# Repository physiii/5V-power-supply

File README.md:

# 5v power supply with a relay for high voltage control.

Combine this with our other devices to get power and control high-voltage switches.

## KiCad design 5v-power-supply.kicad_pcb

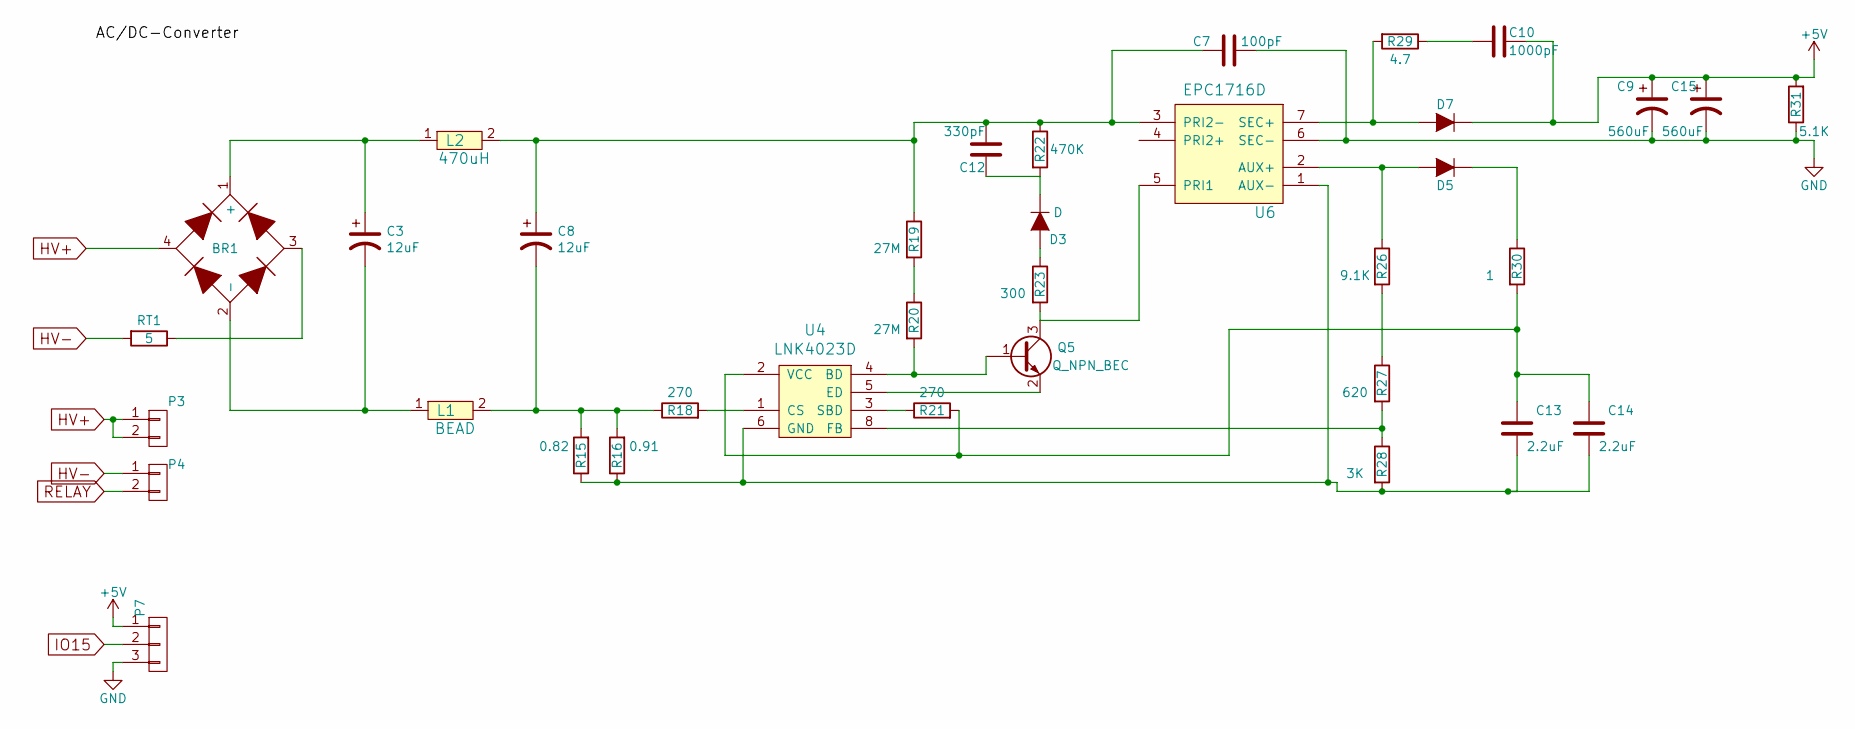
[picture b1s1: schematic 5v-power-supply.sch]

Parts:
BR1: DF08S; DF005S; Part Number DF08SCT
C3, C8: 12uF; C_Radial_D10_L13_P5; Part Number 400AX12MEFC10X12.5
C7: 100pF; C_0603_HandSoldering; Part Number 712-1310-1-ND
C9, C15: 560uF; C_Radial_D8_L11.5_P3.5; Part Number UPW0J561MPD
C10: 1000pF; C_0603_HandSoldering; Part Number GRM188R72E102KW07D
C12: 330pF; C_0805_HandSoldering; Part Number C0805C331KCRACTU
C13, C14: 2.2uF; C_0603_HandSoldering; Part Number C1608X5R1E225K080AB
D3: D; DO-214BA; Part Number GS1MTR
D5: D; SOD-323; Part Number 1N4148WXTPMSCT-ND
D7: D; PMEG45A10EPDAZ-Schottky; Part Number PMEG45A10EPDAZ
L1: BEAD; R_0805_HandSoldering; Part Number MMZ2012D121BT000
L2: 470uH; C_Radial_D10_L13_P5; Part Number BK1608HS330-T
P3, P4: CONN_01X02; pheonix-connector-01x02-5mm; Part Number 277-1667-ND
P7: CONN_01X03; pheonix-connector-01x03-5mm; Part Number ED2792-ND
Q5: Q_NPN_BEC; APT13005SU-G1; Part Number APT13005SU-G1
R15: 0.82; R_0805_HandSoldering; Part Number RL1220S-R82-F
R16: 0.91; R_0805_HandSoldering; Part Number RL1220S-R91-F
R18: 270; R_0805_HandSoldering; Part Number RMCF0805JT270R
R19, R20: 27M; R_1206_HandSoldering; Part Number RV1206JR-0727ML
R21: 270; R_0805_HandSoldering; Part Number RMCF0805JT270RCT-ND
R22: 470K; R_0603_HandSoldering; Part Number RC0603JR-07470KL
R23: 300; R_0603_HandSoldering; Part Number ESR03EZPJ301
R26: 9.1K; R_0603_HandSoldering; Part Number RC0603JR-079K1L
R27: 620; R_0603_HandSoldering; Part Number RC0603JR-07620RL
R28: 3K; R_0603_HandSoldering; Part Number RC0603JR-073KL
R29: 4.7; R_0603_HandSoldering; Part Number RC0603JR-074R7L
R30: 1; R_0603_HandSoldering; Part Number RNCP0603FTD1R00
R31: 5.1K; R_0603_HandSoldering; Part Number RC0603JR-075K1L
RT1: 5; Resistor_Vertical_RM5mm; Part Number SL05 5R001-A
U4: LNK4023D; SO-8; Part Number LNK4023D-TL
U6: EPC1716D; PNK-40230

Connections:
+5V: C9.1, C10.1, C15.1, D7.1 (K), P7.1, R31.2; also elsewhere on the board
GND: C7.2, C9.2, C15.2, P7.3, R31.1, U6.6 (SEC-); also elsewhere on the board
HV+: BR1.4, P3.1, P3.2
HV-: P4.1, RT1.2; also elsewhere on the board
IO15: P7.2; also elsewhere on the board
unnamed: BR1.1 (+), C3.1, L2.1
unnamed: BR1.2 (-), C3.2, L1.1
unnamed: BR1.3, RT1.1
unnamed: C8.2, L1.2, R15.2, R16.2, R18.1
unnamed: C10.2, R29.1
unnamed: C12.1, D3.1 (K), R22.2
unnamed: C7.1, C8.1, C12.2, L2.2, R19.1, R22.1, U6.3 (PRI2-)
unnamed: C13.1, C14.1, R21.2, R30.2, U4.2 (VCC)
unnamed: C13.2, C14.2, R15.1, R16.1, R28.2, U4.6 (GND), U6.1 (AUX-)
unnamed: D3.2 (A), R23.1
unnamed: D5.1 (K), R30.1
unnamed: D5.2 (A), R26.1, U6.2 (AUX+)
unnamed: D7.2 (A), R29.2, U6.7 (SEC+)
unnamed: Q5.1 (B), R20.2, U4.4 (BD)
unnamed: Q5.2 (E), U4.5 (ED)
unnamed: Q5.3 (C), R23.2, U6.5 (PRI1)
unnamed: R18.2, U4.1 (CS)
unnamed: R19.2, R20.1
unnamed: R21.1, U4.3 (SBD)
unnamed: R26.2, R27.1
unnamed: R27.2, R28.1, U4.8 (FB)
RELAY: P4.2; also elsewhere on the board

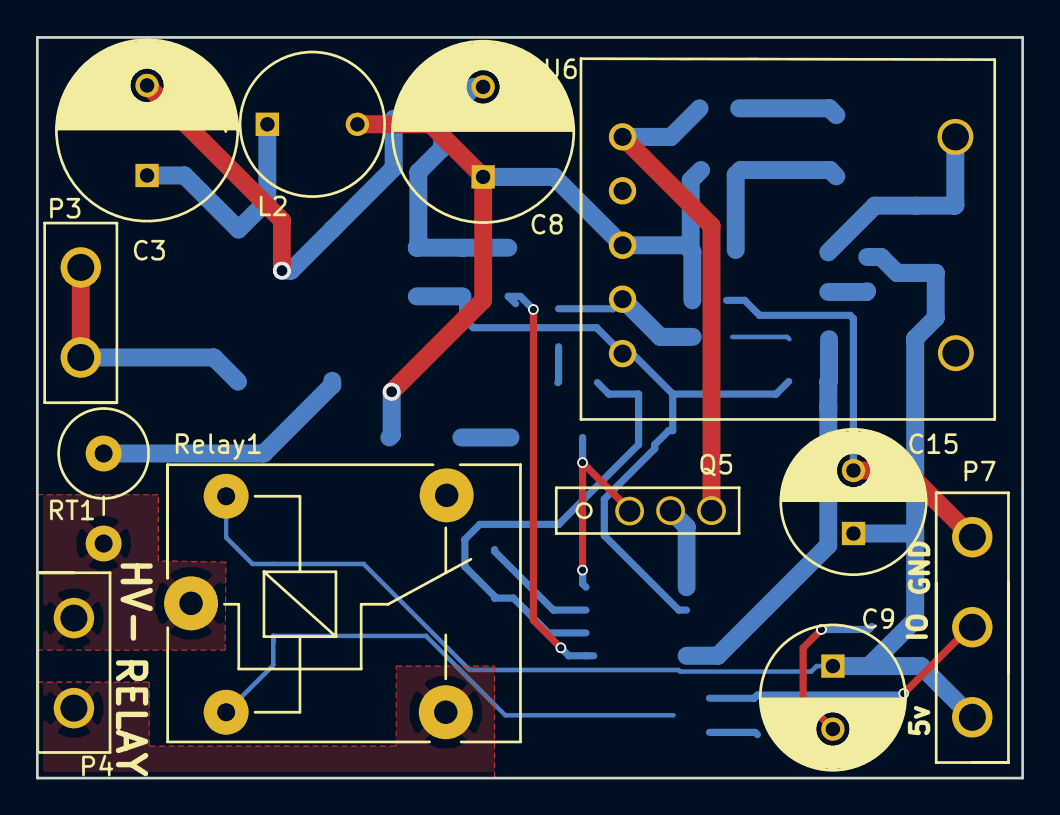
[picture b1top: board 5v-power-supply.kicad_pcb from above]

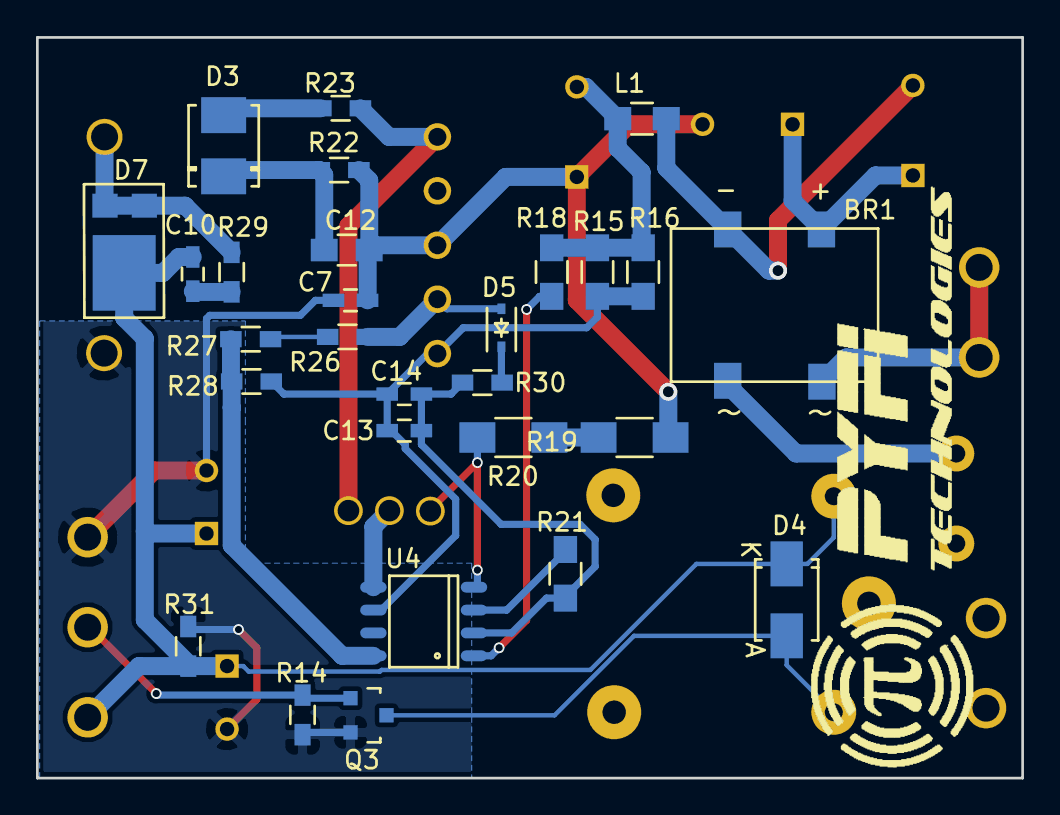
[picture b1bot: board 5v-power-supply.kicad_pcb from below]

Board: 2 copper layers, 54.7 x 41.2 mm, 41 parts (29 on the bottom side), 28 nets.

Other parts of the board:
D4: D; SMA_Standard
LOGO: LOGO
Q3: Q_NPN_BEC; SOT-23
R14: 1K; R_0603_HandSoldering
Relay1: ORWH-SH-105D1F; Relay_SANYOU_SRD_Series_Form_C

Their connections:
+5V: D4.1, Relay1.5; also elsewhere on the board
GND: Q3.2, R14.2; also elsewhere on the board
HV-: Relay1.1; also elsewhere on the board
IO15: Q3.1, R14.1; also elsewhere on the board
unnamed: D4.2, Q3.3, Relay1.2
RELAY: Relay1.3; also elsewhere on the board

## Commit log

2016-08-16 the story so far
2016-11-15 sync.sh update
